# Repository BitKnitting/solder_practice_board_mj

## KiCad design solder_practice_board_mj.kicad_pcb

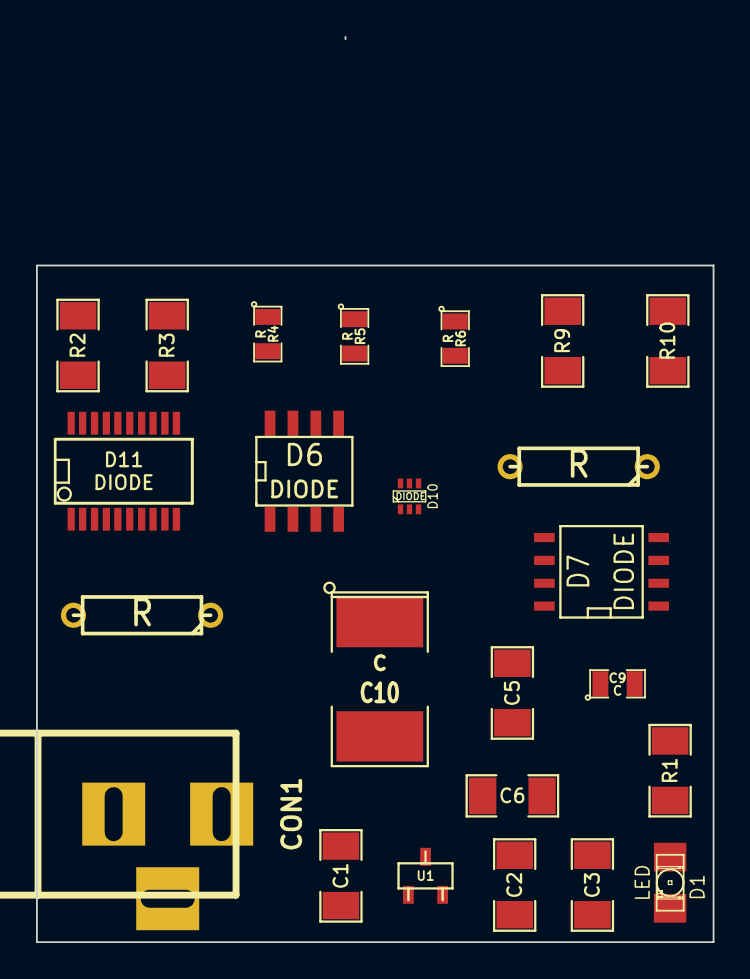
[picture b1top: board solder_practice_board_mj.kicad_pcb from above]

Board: 2 copper layers, 37.6 x 50.3 mm, 24 parts (0 on the bottom side), 4 nets, no tracks yet.

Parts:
C1, C3: 1U; SM1206
C2: 10U; SM1206
C5, C6: C; SM1206
C9: C; SM0805
C10: C; SM2112L
CON1: BARREL_JACK
D1: LED; LED-1206
D6: DIODE; SO8E
D7: DIODE; SO8N
D10: DIODE; SOT363
D11: DIODE; SSOP20
R1: 10K; SM1206
R2, R3, R9, R10: R; SM1206
R4, R5, R6: R; SM0805
R7, R8: R; R3
U1: MCP1703CB; sot23

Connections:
GND: C1.2, C2.2, C3.2, CON1.1, CON1.3, D1.2, U1.1
unnamed: D1.1, R1.2
unnamed: C1.1, CON1.2, U1.3
VCC: C2.1, C3.1, R1.1, U1.2

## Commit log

2014-01-29 Initial commit of CE homework: building a practice solder board
